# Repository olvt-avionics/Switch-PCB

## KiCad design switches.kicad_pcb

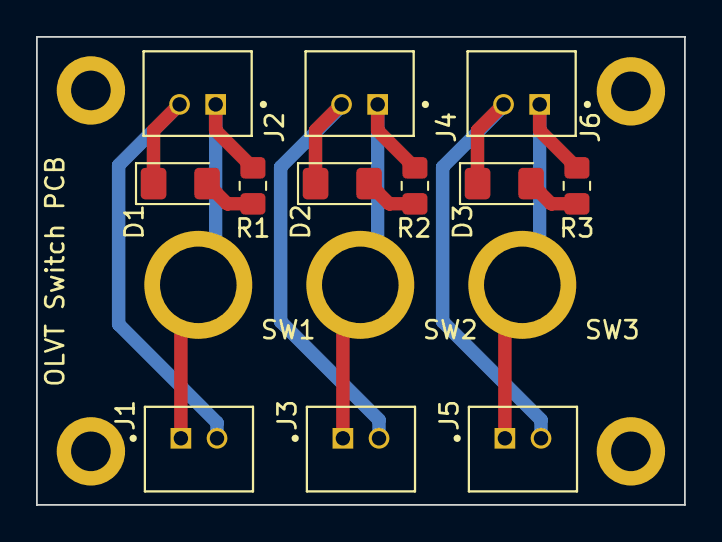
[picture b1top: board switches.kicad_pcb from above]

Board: 2 copper layers, 36.0 x 26.0 mm, 15 parts (0 on the bottom side), 9 nets.

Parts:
D1, D2, D3: LED; LED_1206_3216Metric_Pad1.42x1.75mm_HandSolder
J1, J2, J3, J4, J5, J6: 440054-2; TE_440054-2
R1, R2, R3: 360; R_0805_2012Metric_Pad1.20x1.40mm_HandSolder
SW1, SW2, SW3: SW_Screw; screw switch

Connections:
unnamed: D1.1 (K), J1.2, J2.2
unnamed: D1.2 (A), R1.2
unnamed: D2.1 (K), J3.2, J4.2
unnamed: D2.2 (A), R2.2
unnamed: D3.1 (K), J5.2, J6.2
unnamed: D3.2 (A), R3.2
unnamed: J2.1, R1.1
unnamed: J4.1, R2.1
unnamed: J6.1, R3.1

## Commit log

2023-10-09 Initial files from James
    Use Kicad
